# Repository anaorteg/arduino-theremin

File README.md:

Arduino Theremin
================

Introduction
------------

A fun project to build a theremin with an Arduino-based system. My ultimate goal is to build it into a standalone PCB with an independent ATMega at the control. The source code is stored in the _arduino-source_ directory and schematics are in the Eagle file format in the _schematics_ directory. The project is discussed at the [GeekDad Community](http://geekdad.hotwired.com/group/arduino-theremin) website.

Credits
-------

The original Arduino source code and oscillator schematics are based on:

[Academy of Media Arts Cologne - Theremin as a Capacitive Sensing Device](http://interface.khm.de/index.php/lab/experiments/theremin-as-a-capacitive-sensing-device/)

Additionally, I am looking at using a low-pass filter and DDS technique based on:

[Academy of Media Arts Cologne - Arduino DDS Sinewave Generator](http://interface.khm.de/index.php/lab/experiments/arduino-dds-sinewave-generator/)

Contributing
------------

1. Go to the [GeekDad Arduino Theremin Git-Hub Repository](https://github.com/WiredGeekDad/arduino-theremin).
2. Fork it.
3. Create a branch (`git checkout -b my_arduino_theremin`)
4. Commit your changes (`git commit -am "Added Super Waveform"`)
5. Push to the branch (`git push origin my_arduino_theremin`)
6. Create an [Issue](https://github.com/WiredGeekDad/arduino-theremin/issues) with a link to your branch

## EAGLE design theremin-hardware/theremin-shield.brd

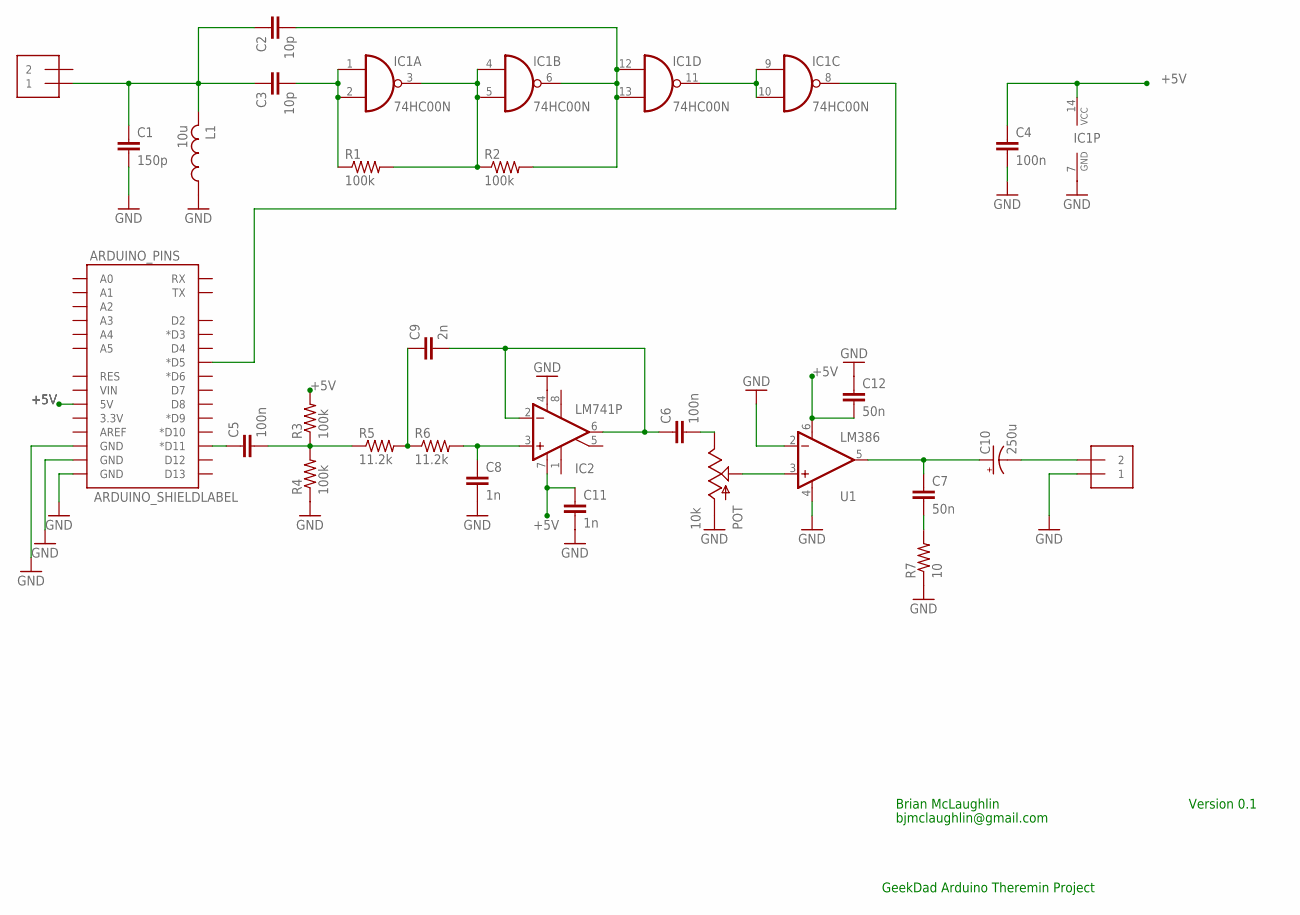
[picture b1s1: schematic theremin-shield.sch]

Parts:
ARDUINO_PINS: ARDUINO_SHIELDLABEL; DUEMILANOVE_SHIELD
C1: 150p; CAP-PTH-SMALL
C2, C3: 10p; CAP-PTH-SMALL
C4: 100n; CAP-PTH-SMALL
C5, C6: 100n; CAP-PTH-LARGE
C7, C12: 50n; CAP-PTH-SMALL2
C8, C11: 1n; CAP-PTH-SMALL2
C9: 2n; CAP-PTH-SMALL2
C10: 250u; CPOL-RADIAL-1000UF-25V
IC1: 74HC00N; DIL14
IC2: LM741P; DIL08
J1, J2: 1X2-3.5MM
L1: 10u; 0204/7
POT: 10k; ALPS_POT
R1, R2, R3, R4: 100k; AXIAL-0.4
R5, R6: 11.2k; AXIAL-0.4
R7: 10; AXIAL-0.4
U1: LM386; DIP08

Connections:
+5V: ARDUINO_PINS.5V, C4.1, C11.1, C12.2, IC1.14 (VCC), IC2.7 (V+), R3.P$2 (2), U1.6 (V+)
GND: ARDUINO_PINS.GND@0 (GND), ARDUINO_PINS.GND@1 (GND), ARDUINO_PINS.GND@2 (GND), C1.2, C4.2, C8.2, C11.2, C12.1, IC1.7 (GND), IC2.4 (V-), J1.1, L1.1, POT.P$3 (A), R4.P$1 (1), R7.P$1 (1), U1.2 (-IN), U1.4 (V-)
unnamed: C3.2, IC1.1 (I0), IC1.2 (I1), R1.P$1 (1)
unnamed: IC1.3 (O), IC1.4 (I0), IC1.5 (I1), R1.P$2 (2), R2.P$1 (1)
unnamed: ARDUINO_PINS.D11 (*D11), C5.1
unnamed: C2.2, IC1.6 (O), IC1.12 (I0), IC1.13 (I1), R2.P$2 (2)
unnamed: C1.1, C2.1, C3.1, J2.1, L1.2
unnamed: IC1.9 (I0), IC1.10 (I1), IC1.11 (O)
unnamed: ARDUINO_PINS.D5 (*D5), IC1.8 (O)
unnamed: C6.1, C9.2, IC2.2 (-IN), IC2.6 (OUT)
unnamed: C5.2, R3.P$1 (1), R4.P$2 (2), R5.P$1 (1)
unnamed: C8.1, IC2.3 (+IN), R6.P$2 (2)
unnamed: C6.2, POT.P$1 (E)
unnamed: C9.1, R5.P$2 (2), R6.P$1 (1)
unnamed: POT.P$2 (S), U1.3 (+IN)
unnamed: C7.1, C10.1 (+), U1.5 (OUT)
unnamed: C7.2, R7.P$2 (2)
unnamed: C10.2 (-), J1.2

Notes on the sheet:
Version 0.1
Brian McLaughlin
bjmclaughlin@gmail.com
GeekDad Arduino Theremin Project

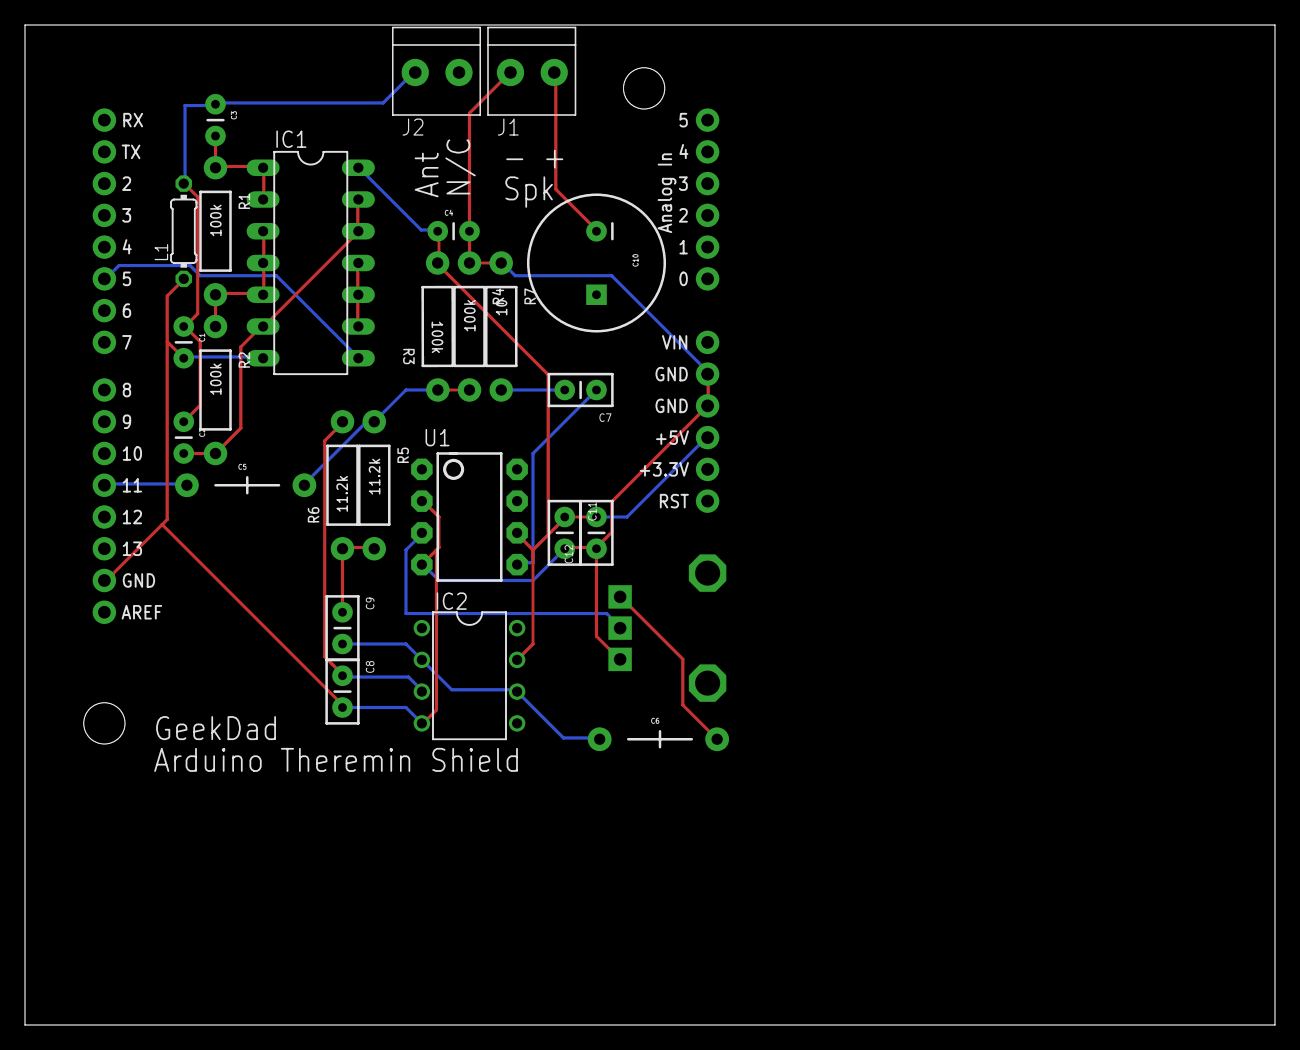
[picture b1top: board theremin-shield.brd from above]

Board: 2 copper layers, 100.0 x 80.0 mm, 27 parts (0 on the bottom side), 18 nets.

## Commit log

2012-04-11 Baseline Code & Schematics
2012-04-11 File Removed From Wrong Locationc
2012-04-11 Added README
2012-04-12 Fixed Arduino Foder Structure
2012-04-12 Changed hardware directory to work better with Eagle.
2012-04-25 Repository moved to GeekDad organization.
2012-04-25 GeekDad Rebaseline
2012-05-24 Major updates after Maker Faire 2012
    Created the PCB as an Arduino Shield. Also, there is now only one ISR
    necessary. I believe both the hardware and software need some tweaking
    and tuning but I am definitely getting there.

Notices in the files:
parts and their libraries:
SparkFun: Licensing: CC v3.0 Share-Alike You are welcome to use this library for commercial purposes.
